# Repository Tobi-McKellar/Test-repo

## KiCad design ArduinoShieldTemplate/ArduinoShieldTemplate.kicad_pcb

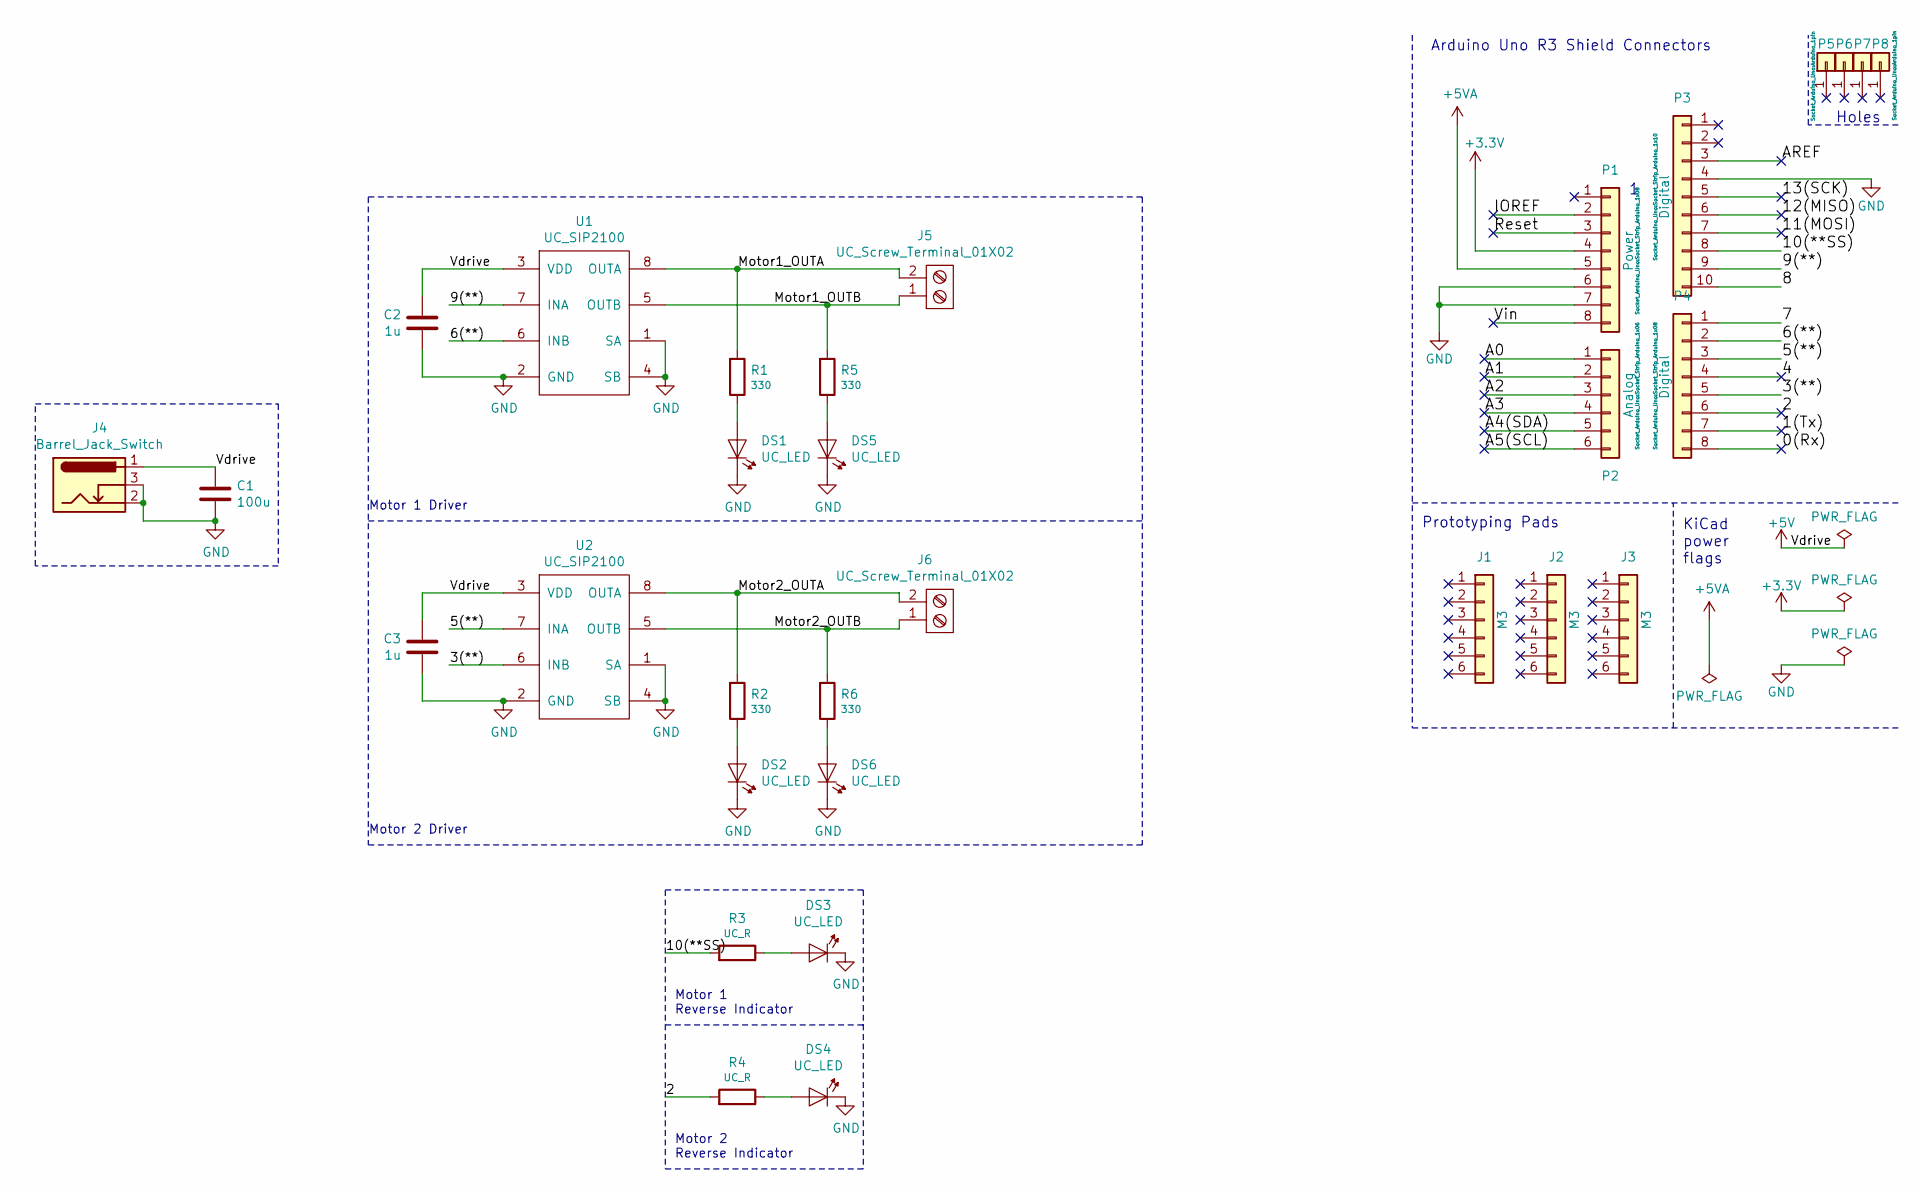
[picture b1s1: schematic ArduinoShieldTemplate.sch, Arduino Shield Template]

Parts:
C1: 100u; C_Rect_L7.0mm_W2.5mm_P5.00mm
C2, C3: 1u; C_Rect_L7.0mm_W2.5mm_P5.00mm
DS1, DS2, DS3, DS4, DS5, DS6: UC_LED; LED_D5.0mm
J1, J2, J3: M3; PinHeader_1x06_P2.54mm_Vertical
J4: Barrel_Jack_Switch; BarrelJack_Horizontal
J5, J6: UC_Screw_Terminal_01X02; TerminalBlock_Phoenix_MKDS-1,5-2-5.08_1x02_P5.08mm_Horizont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
P1: Power; Socket_Strip_Arduino_1x08
P2: Analog; Socket_Strip_Arduino_1x06
P3: Digital; Socket_Strip_Arduino_1x10
P4: Digital; Socket_Strip_Arduino_1x08
P5, P6, P7, P8: CONN_01X01; Arduino_1pin
R1, R2, R5, R6: 330; R_Axial_DIN0207_L6.3mm_D2.5mm_P7.62mm_Horizontal
R3, R4: UC_R; R_Axial_DIN0207_L6.3mm_D2.5mm_P7.62mm_Horizontal
U1, U2: UC_SIP2100; SOIC-8_3.9x4.9mm_P1.27mm

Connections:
+3V3: P1.4
+5V: C1.1, C2.2, C3.2, J4.1, U1.3 (VDD), U2.3 (VDD)
+5VA: P1.5
/0(Rx): P4.8
/1(Tx): P4.7
/2: P4.6, R4.1
/3(**): P4.5, U2.6 (INB)
/4: P4.4
/5(**): P4.3, U2.7 (INA)
/6(**): P4.2, U1.6 (INB)
/7: P4.1
/8: P3.10
/9(**): P3.9, U1.7 (INA)
/10(**SS): P3.8, R3.1
/11(MOSI): P3.7
/12(MISO): P3.6
/13(SCK): P3.5
/A0: P2.1
/A1: P2.2
/A2: P2.3
/A3: P2.4
/A4(SDA): P2.5
/A5(SCL): P2.6
/AREF: P3.3
/IOREF: P1.2
/Motor1_OUTA: J5.2, R1.1, U1.8 (OUTA)
/Motor1_OUTB: J5.1, R5.1, U1.5 (OUTB)
/Motor2_OUTA: J6.2, R2.1, U2.8 (OUTA)
/Motor2_OUTB: J6.1, R6.1, U2.5 (OUTB)
/Reset: P1.3
/Vin: P1.8
GND: C1.2, C2.1, C3.1, DS1.1 (K), DS2.1 (K), DS3.1 (K), DS4.1 (K), DS5.1 (K), DS6.1 (K), J4.2, J4.3, P1.6, P1.7, P3.4, U1.1 (SA), U1.2 (GND), U1.4 (SB), U2.1 (SA), U2.2 (GND), U2.4 (SB)
unnamed: DS1.2 (A), R1.2
unnamed: DS2.2 (A), R2.2
unnamed: DS3.2 (A), R3.2
unnamed: DS4.2 (A), R4.2
unnamed: DS5.2 (A), R5.2
unnamed: DS6.2 (A), R6.2

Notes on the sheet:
Holes
Arduino Uno R3 Shield Connectors
KiCad power flags
Prototyping Pads
Motor 1 Driver
Motor 2 Driver
Motor 1 Reverse Indicator
Motor 2 Reverse Indicator

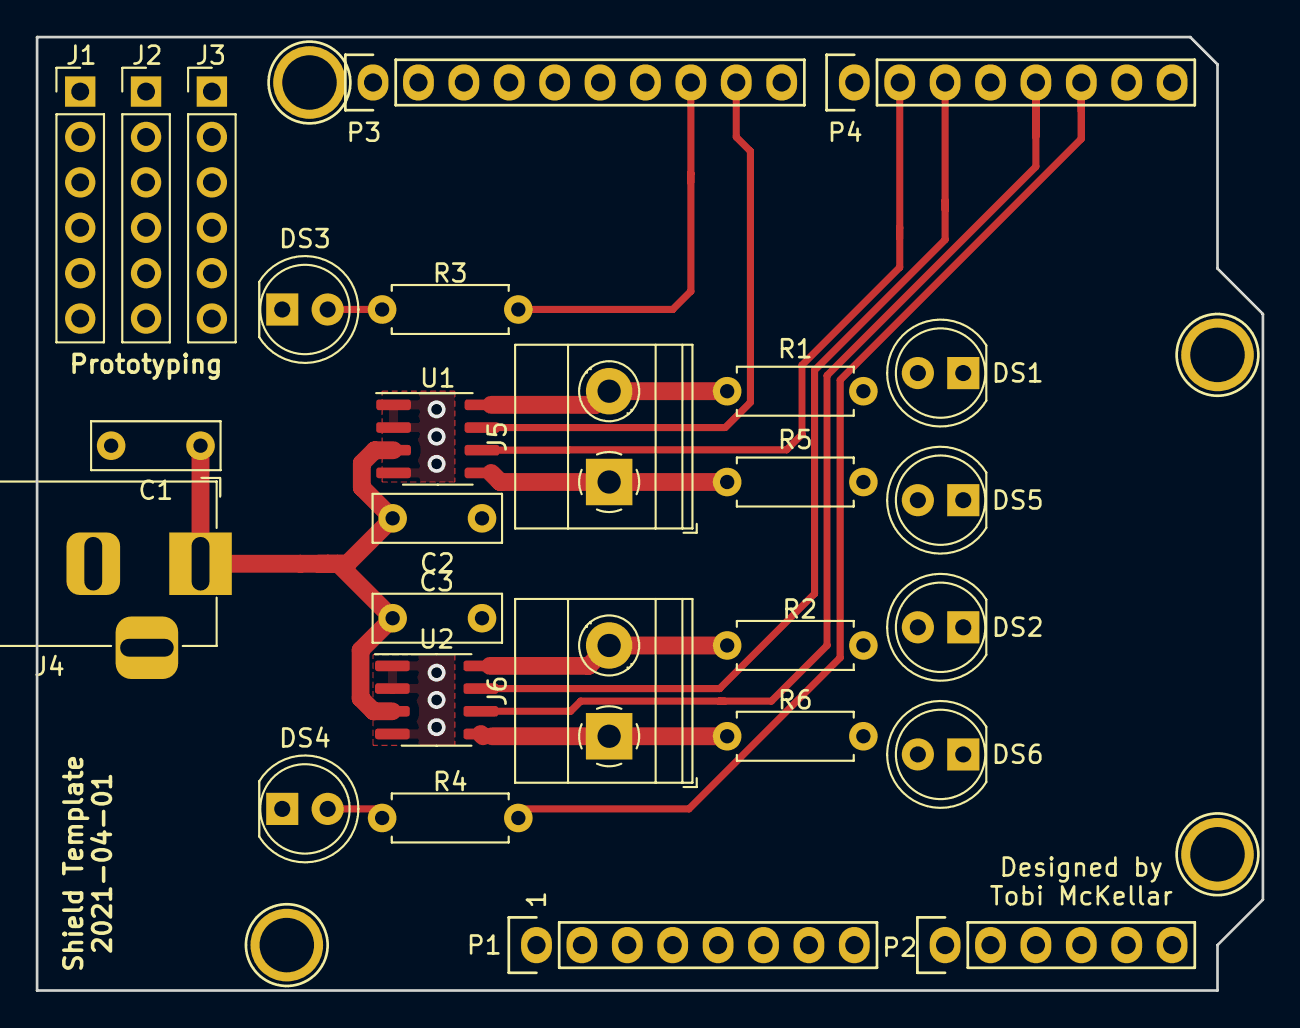
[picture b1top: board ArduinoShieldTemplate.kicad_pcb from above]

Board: 2 copper layers, 68.6 x 53.3 mm, 31 parts (0 on the bottom side), 18 nets.

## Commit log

2022-07-22 Testing how git works
2022-07-22 Testing branches
2022-07-22 Revert "Testing branches"
2022-07-23 I redesigned the motor shield - could be a good starting point for the project[O
2022-07-23 cheeky rewiring for aesthetics
2022-07-23 Fixing up the stuff design rules checker pointed out
